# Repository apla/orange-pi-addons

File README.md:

# Orange Pi Zero+ H5 Addons

## Hacking Addon

## TODO: DeviceTree

[Armbian docs for using overlays](https://docs.armbian.com/User-Guide_Allwinner_overlays/)

https://elinux.org/Device_Tree_Usage

[DTS for OrangePi Zero H2+](https://github.com/torvalds/linux/blob/master/arch/arm/boot/dts/sun8i-h2-plus-orangepi-zero.dts)

[DTS for OrangePi Zero H5](https://github.com/torvalds/linux/blob/master/arch/arm64/boot/dts/allwinner/sun50i-h5-orangepi-zero-plus.dts)

https://forum.armbian.com/topic/8795-next-lts-kernel-419y-allwinner-a10-a20-a64-h2-h3-h5-h6-debugging-party/?do=findComment&comment=67014

adding voltage regulator

```js
	reg_vdd_cpux: vdd-cpux-regulator {
		compatible = "regulator-gpio";
		regulator-name = "vdd-cpux";
		regulator-type = "voltage";
		regulator-boot-on;
		regulator-always-on;
		regulator-min-microvolt = <1100000>;
		regulator-max-microvolt = <1300000>;
		regulator-ramp-delay = <50>; /* 4ms */

		gpios = <&r_pio 0 6 GPIO_ACTIVE_HIGH>; /* PA6 */
		enable-active-high;
		gpios-states = <0>;
		states = <1100000 0
			  1300000 1>;
	};
```

```js
&cpu0 {
	cpu-supply = <&reg_vdd_cpux>;
};
```

adding usb power switch (https://www.kernel.org/doc/Documentation/devicetree/bindings/regulator/fixed-regulator.txt)

```js
	usb_pwr: usb_pwr {
		compatible = "regulator-fixed";
		regulator-name = "vbus-addon-supply";
		regulator-min-microvolt = <5000000>;
		regulator-max-microvolt = <5000000>;
		gpio = <&r_pio 0 7>;
		regulator-boot-on;
	};
```

[ina219 dt overlay](https://github.com/armbian/sunxi-DT-overlays/blob/master/examples/i2c-ina219.dts)

```js
/dts-v1/;
/plugin/;

/ {
	compatible = "allwinner,sun4i-a10", "allwinner,sun7i-a20", "allwinner,sun8i-h3", "allwinner,sun50i-a64", "allwinner,sun50i-h5";

	fragment@0 {
		target = <&i2c0>;
		__overlay__ {
			#address-cells = <1>;
			#size-cells = <0>;
			ina219@40 {
				compatible = "ti,ina219";
				reg = <0x40>;
				status = "okay";
				shunt-resistor = <100000>;
			};
		};
	};
};
```

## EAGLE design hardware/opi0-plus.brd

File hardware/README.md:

# HW status: your OPi will burn with flames!

## Hardware issues after manufacture

 * **MAJOR** There is a one short circuit between 5V and GND on USB connector shield
 * 3.5 AV connector placed upside down
 * Current shunt placed after USB, so current meter shows junk after USB power shut down
 * No filtering capacitors for temp and security devices

## What works

 * I2C works fine
 * USB works fine (data, power switching, power metering)

## What untested

 * ESD on USB
 * USB overcurrent indicator
 * UART + UART level shift
 * SPI
 * AV, Mic
 * PWM

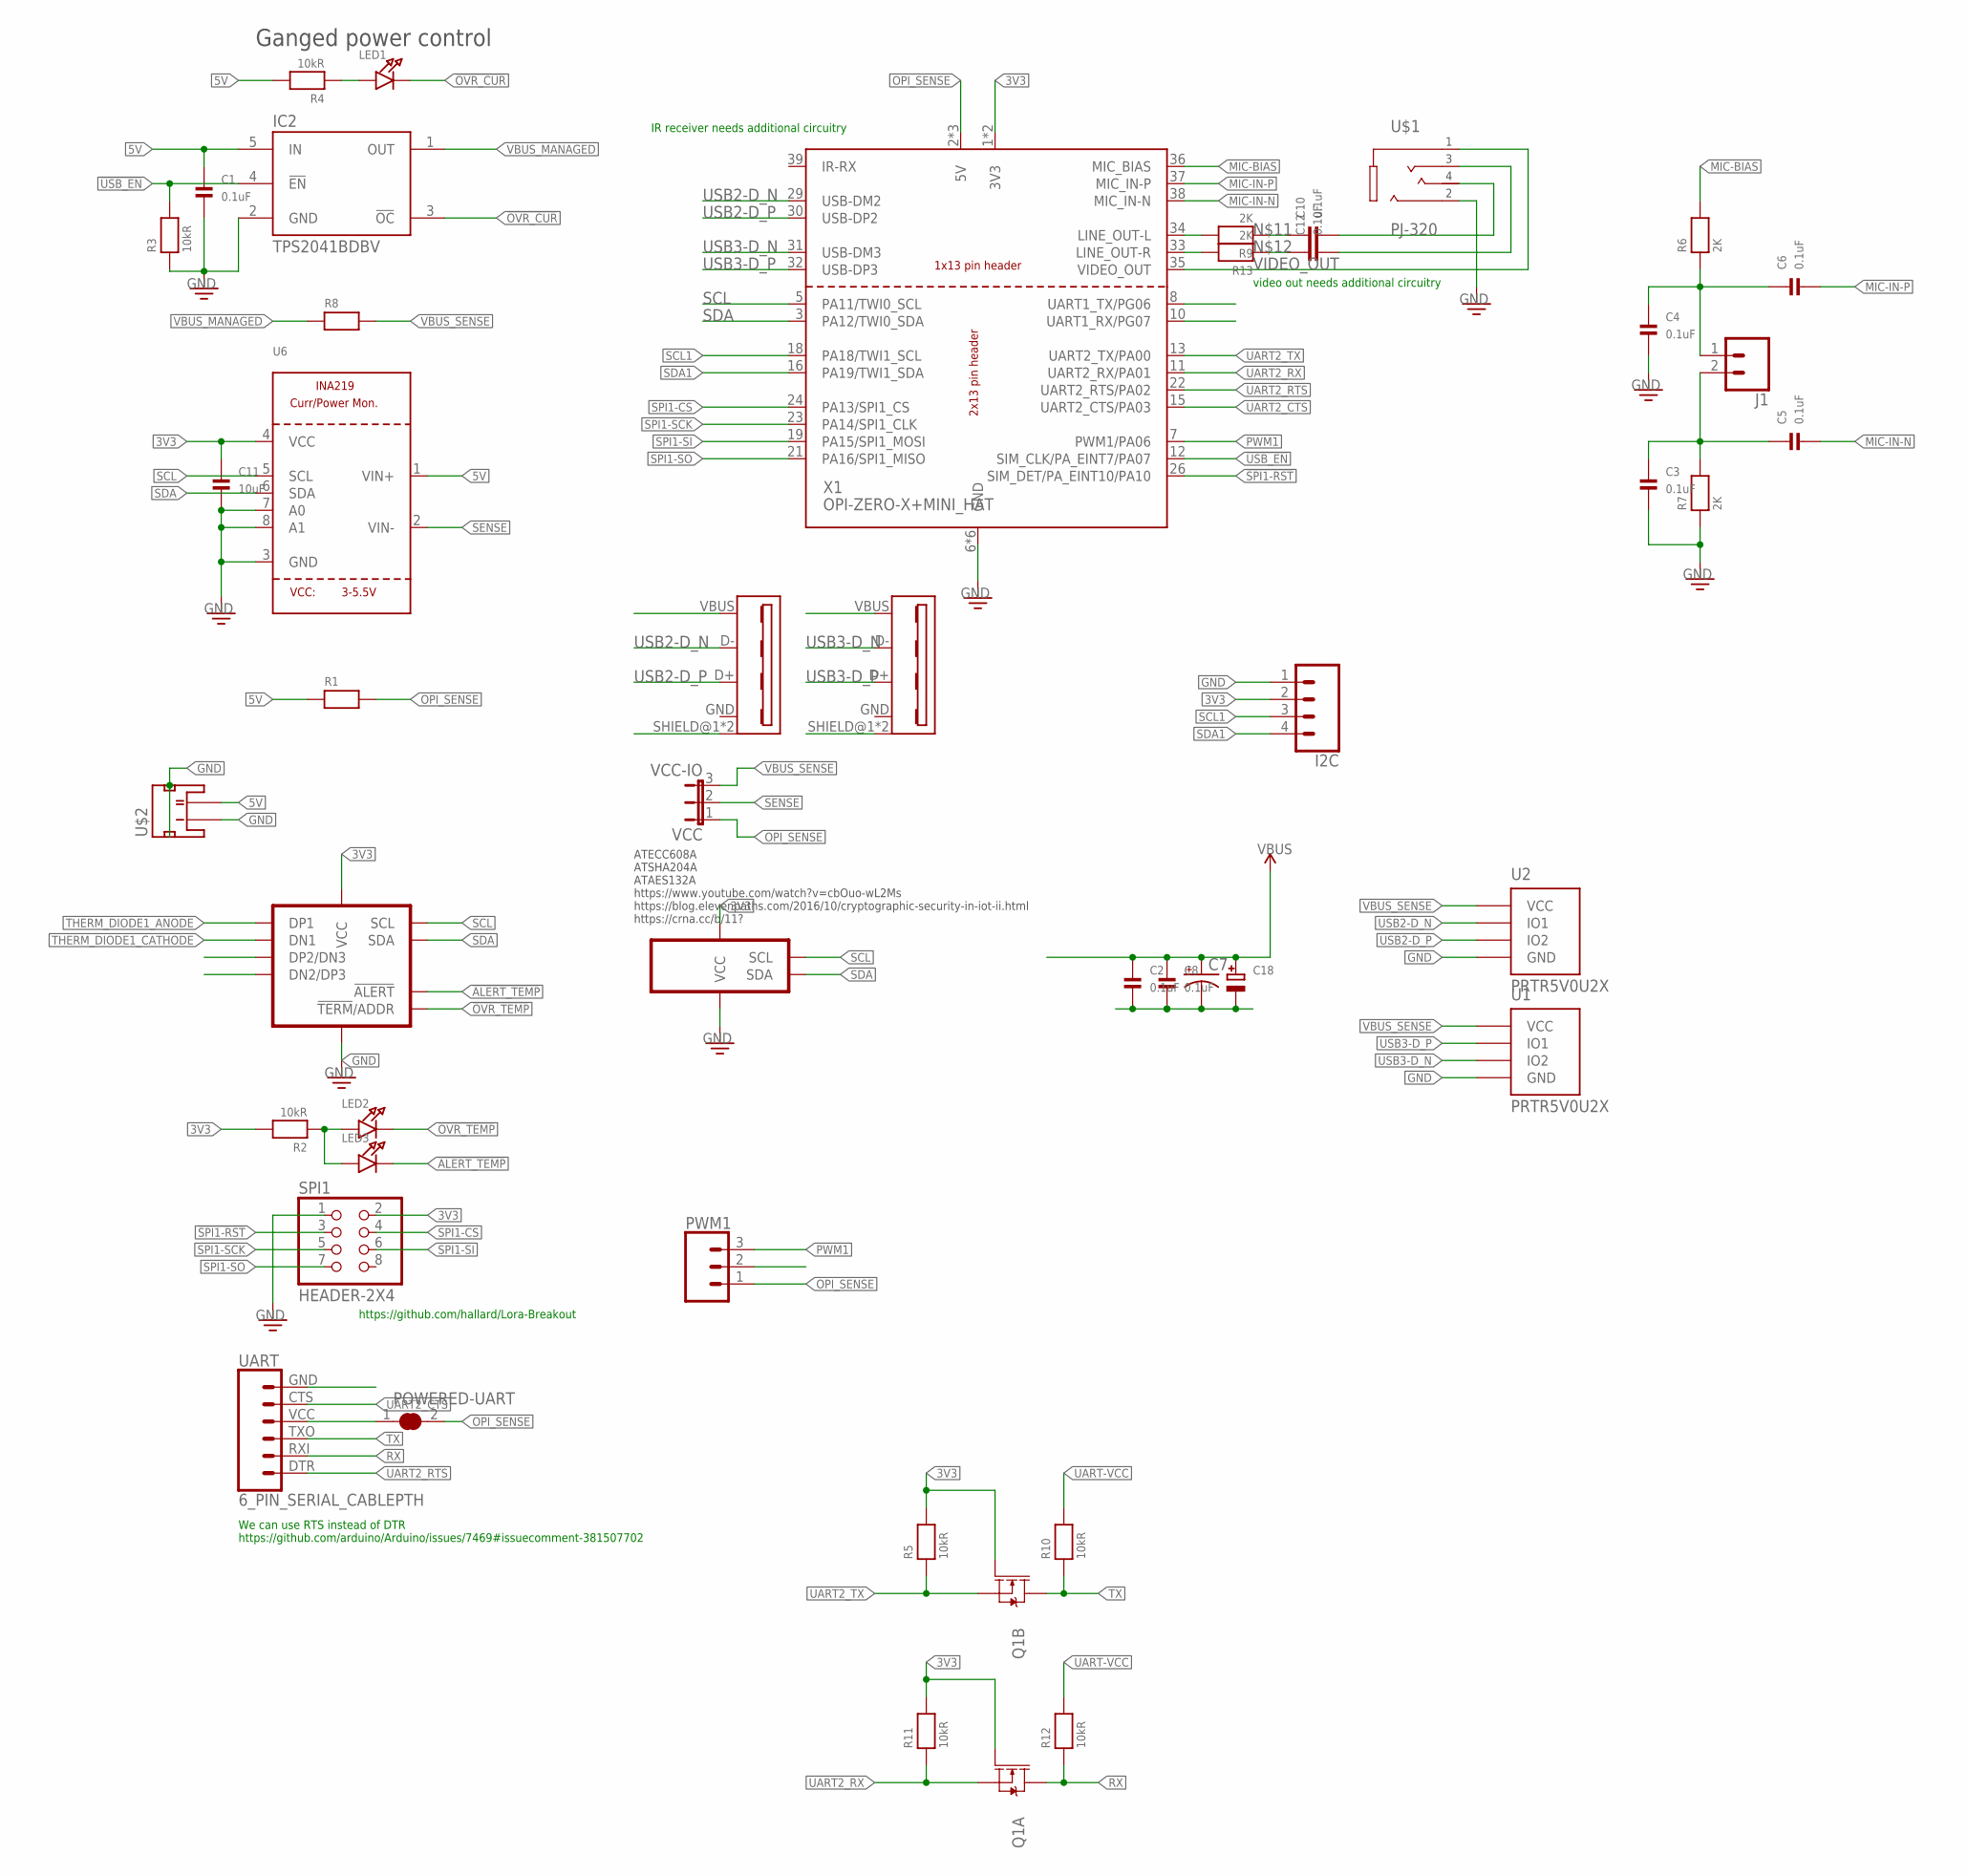
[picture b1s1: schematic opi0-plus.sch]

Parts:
C1, C2, C3, C4, C5, C6, C8, C10, C12: 0.1uF; _0603MP
C7: CAP_POLD; PANASONIC_D
C11: 10uF; _0603MP
C18: CAP_ELECTROLYTICPTH_3.5MMGRID_8MMDIA; CELEC_3.5MM_8MM
I2C: CONN_04; 1X04
IC2: TPS2041BDBV; SOT23-5L
J1: CONN_02; 1X02
LED1, LED2, LED3: LED0603_NOOUTLINE; CHIPLED_0603_NOOUTLINE
POWERED-UART: SOLDERJUMPER_CLOSED; SOLDERJUMPER_CLOSEDWIRE
PWM1: CONN_03JST-PTH-VERT; JST-3-PTH-VERT
Q1: MOSFET_NCH_DUAL-IRF5852; SOT23-6
R1, R8: RESISTOR1206; 1206
R2, R3, R4, R5, R10, R11, R12: 10kR; _0603MP
R6, R7, R9, R13: 2K; _0603MP
SPI1: HEADER-2X4; 2X04
U1, U2: PRTR5V0U2X; SOT-143B
U6: INA219; SOT23-8
U$1: PJ-320
U$2: JST-PH-2P; JST-PH-SMD
U$3: MCP9904; VDFN-10-0.5-3X3
U$5: ATECC508A-MAH; UDFN-8-0.5-3X2
UART: 6_PIN_SERIAL_CABLEPTH; FTDI_BASIC
USB1, USB2: USB-A-FA-F-PTH; USB-A-F-PTH
VCC: VCC-IO; JUMPER3
X1: OPI-ZERO-X+MINI_HAT; OPI0+MINI_HAT

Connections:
3V3: C11.1, I2C.2, Q1.1 (G), Q1.3 (G), R2.2, R5.2, R11.2, SPI1.2, U6.4 (VCC), U$3.P1 (VCC), U$5.P8 (VCC), X1.1 (3V3), X1.17 (3V3)
5V: C1.1, IC2.5 (IN), R1.1, R4.2, U6.1 (VIN+), U$2.2
!ALERT_TEMP: LED3.C, U$3.P8 (!ALERT)
!OVR_CUR: IC2.3 (!OC), LED1.C
!OVR_TEMP: LED2.C, U$3.P7 (!TERM!/ADDR)
!SPI1-RST!: SPI1.3, X1.26 (SIM_DET/PA_EINT10/PA10)
!USB_EN: IC2.4 (!EN), R3.2, X1.12 (SIM_CLK/PA_EINT7/PA07)
GND: C1.2, C2.2, C3.2, C4.2, C7.-, C8.2, C11.2, C18.-, I2C.1, IC2.2 (GND), PWM1.2, R3.1, R7.1, SPI1.1, U1.1 (GND), U2.1 (GND), U6.3 (GND), U6.7 (A0), U6.8 (A1), U$1.2_1 (2), U$2.1, U$2.SOL@1 (PAD1), U$2.SOL@2 (PAD2), U$3.P6 (GND), U$5.P4 (GND), UART.GND (6), USB1.GND, USB1.SHIELD@1 (SHIELD), USB1.SHIELD@2 (SHIELD), USB2.GND, USB2.SHIELD@1 (SHIELD), USB2.SHIELD@2 (SHIELD), X1.6 (GND), X1.9 (GND), X1.14 (GND), X1.20 (GND), X1.25 (GND), X1.28 (GND)
LINE-L: C10.2, U$1.4_1 (4)
LINE-R: C12.2, U$1.3
MIC-BIAS: R6.2, X1.36 (MIC_BIAS)
MIC-IN-N: C5.2, X1.38 (MIC_IN-N)
MIC-IN-P: C6.2, X1.37 (MIC_IN-P)
unnamed: LED2.A, LED3.A, R2.1
unnamed: C4.1, C6.1, J1.1, R6.1
unnamed: C3.1, C5.1, J1.2, R7.2
unnamed: LED1.A, R4.1
unnamed: R9.2, X1.34 (LINE_OUT-L)
unnamed: R13.2, X1.33 (LINE_OUT-R)
unnamed: C10.1, R9.1
unnamed: C12.1, R13.1
OPI_SENSE: POWERED-UART.2, PWM1.1, R1.2, VCC.1, X1.2 (5V), X1.4 (5V), X1.27 (5V)
PWM1: PWM1.3, X1.7 (PWM1/PA06)
RX: Q1.6 (D), R12.1, UART.RXI (2)
SCL: U6.5 (SCL), U$3.P10 (SCL), U$5.P6 (SCL), X1.5 (PA11/TWI0_SCL)
SCL1: I2C.3, X1.18 (PA18/TWI1_SCL)
SDA: U6.6 (SDA), U$3.P9 (SDA), U$5.P5 (SDA), X1.3 (PA12/TWI0_SDA)
SDA1: I2C.4, X1.16 (PA19/TWI1_SDA)
SENSE: U6.2 (VIN-), VCC.2
SPI1-CS: SPI1.4, X1.24 (PA13/SPI1_CS)
SPI1-SCK: SPI1.5, X1.23 (PA14/SPI1_CLK)
SPI1-SI: SPI1.6, X1.19 (PA15/SPI1_MOSI)
SPI1-SO: SPI1.7, X1.21 (PA16/SPI1_MISO)
THERM_DIODE1_ANODE: U$3.P2 (DP1)
THERM_DIODE1_CATHODE: U$3.P3 (DN1)
TX: Q1.4 (D), R10.1, UART.TXO (3)
UART2_CTS: UART.CTS (5), X1.15 (UART2_CTS/PA03)
UART2_RTS: UART.DTR (1), X1.22 (UART2_RTS/PA02)
UART2_RX: Q1.5 (S), R11.1, X1.11 (UART2_RX/PA01)
UART2_TX: Q1.2 (S), R5.1, X1.13 (UART2_TX/PA00)
UART-VCC: POWERED-UART.1, R10.2, R12.2, UART.VCC (4)
USB2-D_N: U2.2 (IO1), USB1.D-, X1.29 (USB-DM2)
USB2-D_P: U2.3 (IO2), USB1.D+, X1.30 (USB-DP2)
USB3-D_N: U1.3 (IO2), USB2.D-, X1.31 (USB-DM3)
USB3-D_P: U1.2 (IO1), USB2.D+, X1.32 (USB-DP3)
VBUS_MANAGED: IC2.1 (OUT), R8.1
VBUS_SENSE: C2.1, C7.+, C8.1, C18.+, R8.2, U1.4 (VCC), U2.4 (VCC), USB1.VBUS, USB2.VBUS, VCC.3
VIDEO_OUT: U$1.1, X1.35 (VIDEO_OUT)

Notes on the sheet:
Ganged power control
We can use RTS instead of DTR https://github.com/arduino/Arduino/issues/7469#issuecomment-381507702
ATECC608A ATSHA204A ATAES132A https://www.youtube.com/watch?v=cbOuo-wL2Ms https://blog.elevenpaths.com/2016/10/cryptographic-security-in-iot-ii.html https://crna.cc/b/11?
https://github.com/hallard/Lora-Breakout
video out needs additional circuitry
IR receiver needs additional circuitry

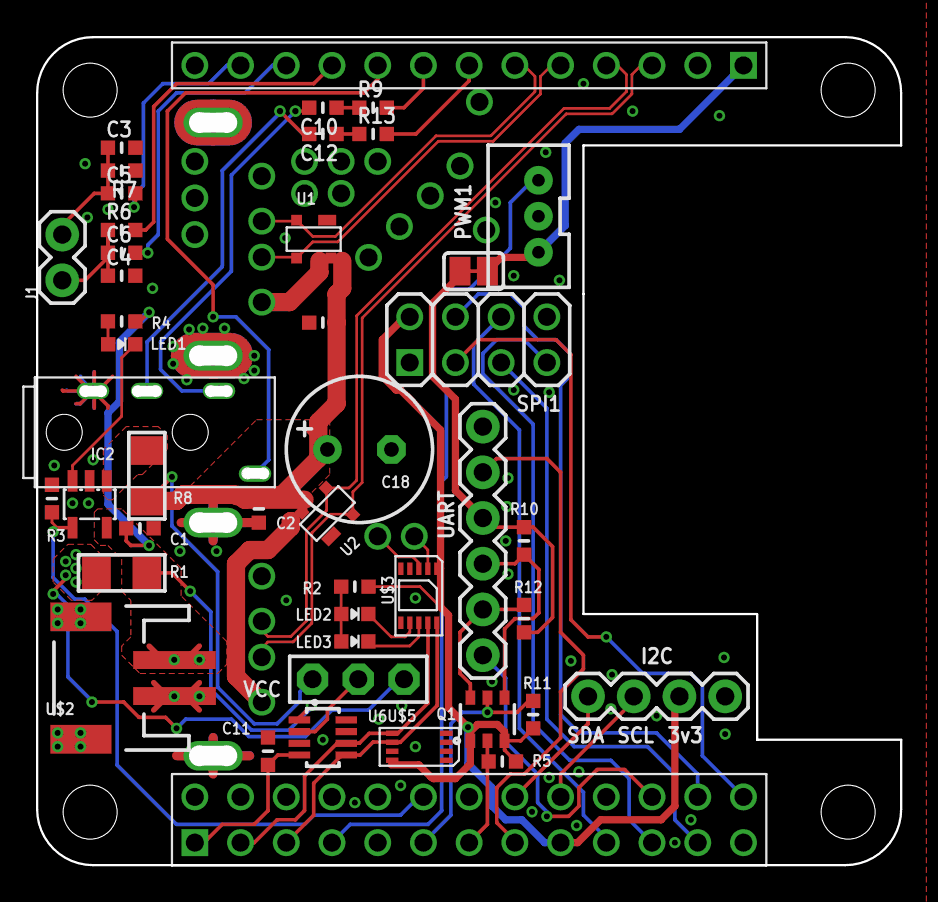
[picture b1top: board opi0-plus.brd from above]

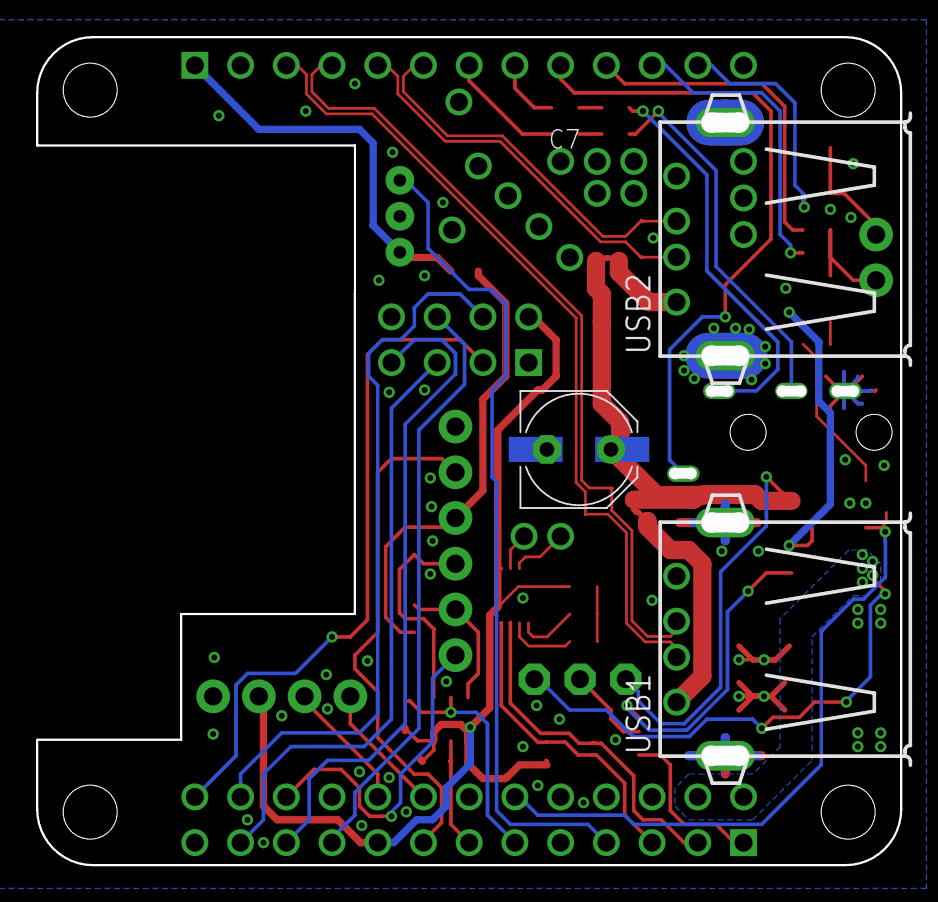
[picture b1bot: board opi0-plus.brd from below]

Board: 2 copper layers, 47.0 x 45.0 mm, 47 parts (3 on the bottom side), 46 nets.

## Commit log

2018-12-14 initial revision + pcb
2018-12-14 hardware status to avoid complaints
2018-12-20 addon image with current status

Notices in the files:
parts and their libraries:
microbuilder: This work is placed in the public domain, and may be freely used for commercial and non-commercial work with the following conditions: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
SparkFun-Passives: Licensing: Creative Commons ShareAlike 4.0 International - https://creativecommons.org/licenses/by-sa/4.0
